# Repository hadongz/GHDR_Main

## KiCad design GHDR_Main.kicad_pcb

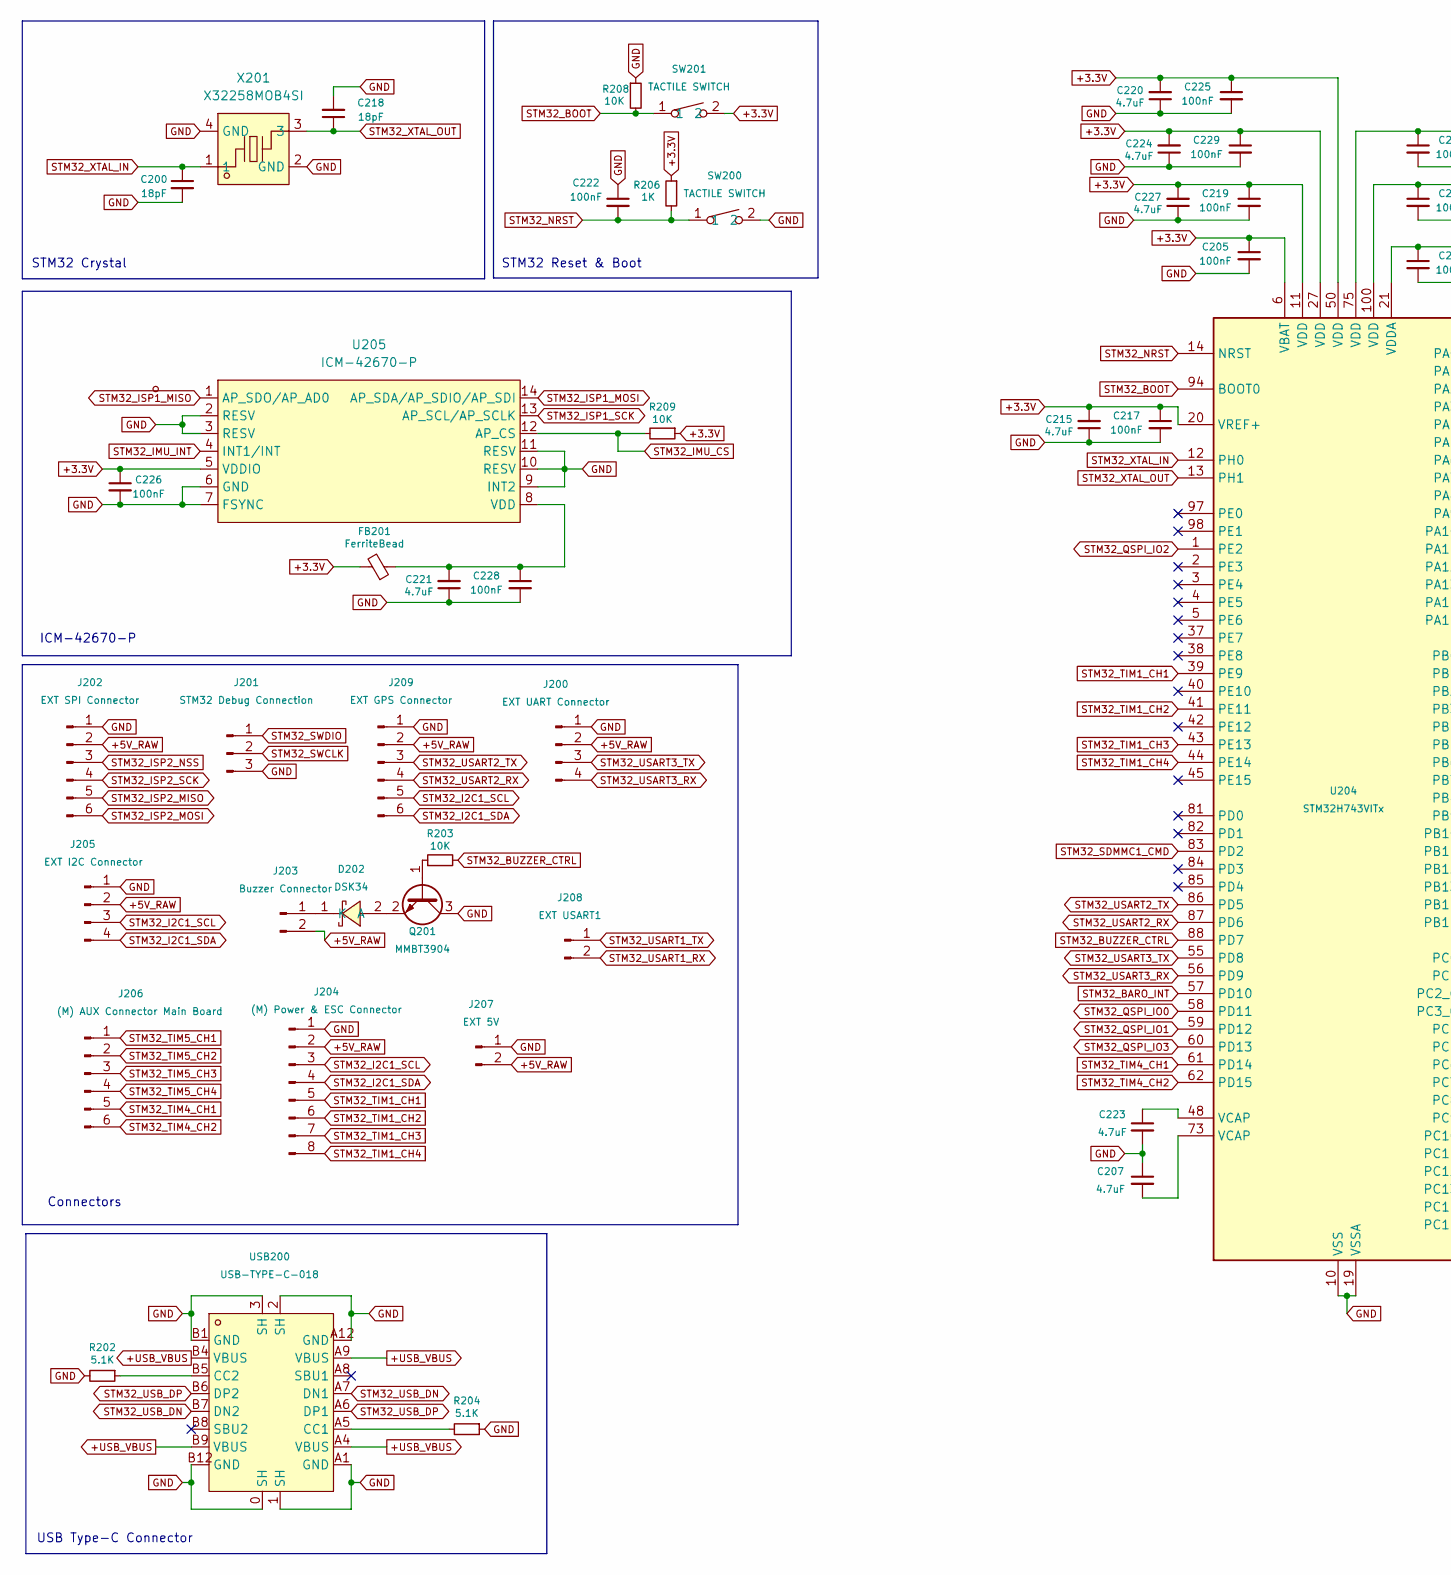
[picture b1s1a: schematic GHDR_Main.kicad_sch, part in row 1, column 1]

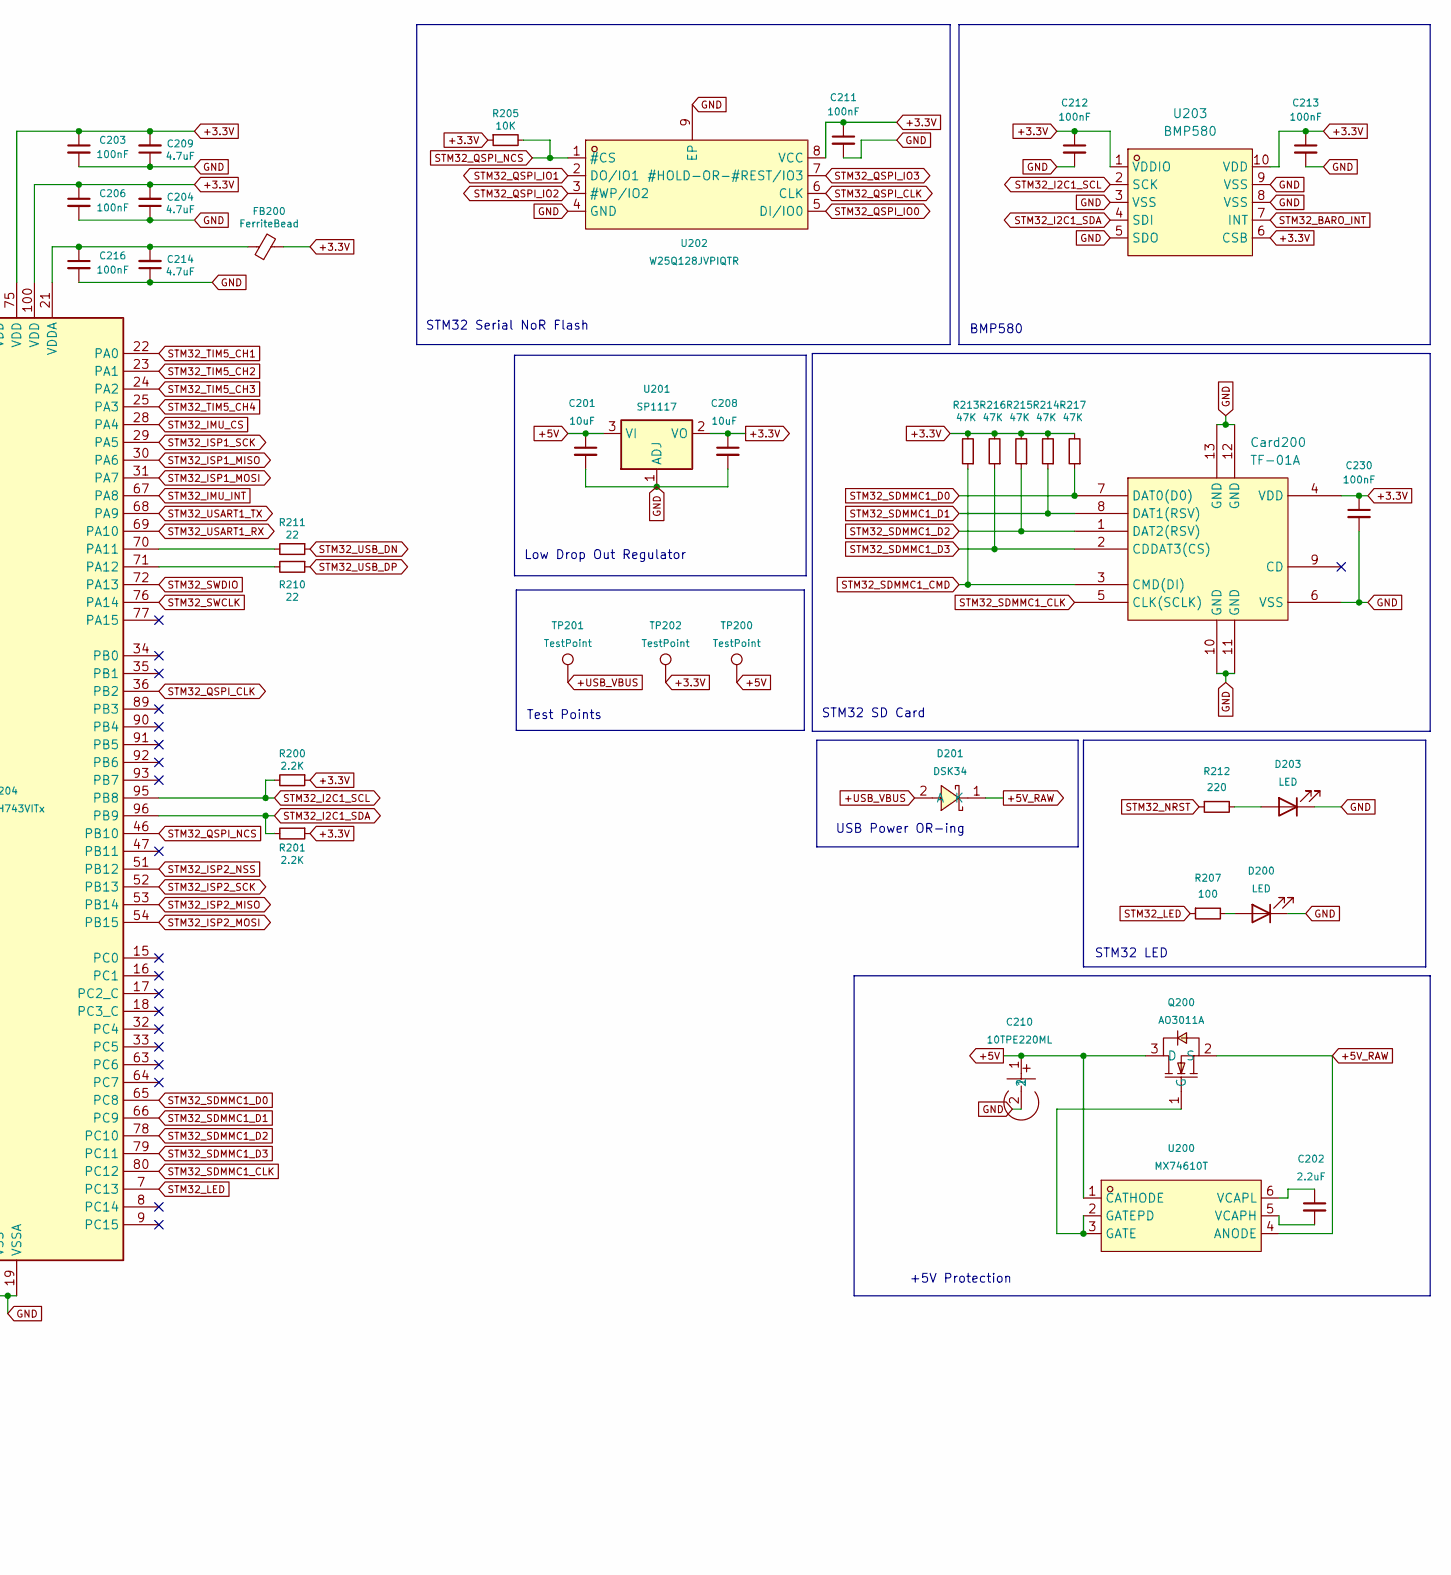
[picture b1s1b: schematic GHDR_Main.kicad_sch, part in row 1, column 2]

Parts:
C200, C218: 18pF; C_0603_1608Metric; LCSC Part C105620
C201, C208: 10uF; C_0805_2012Metric; LCSC Part C7432781
C202: 2.2uF; C_0805_2012Metric; LCSC Part C108719
C203, C205, C206, C211, C212, C213, C216, C217, C219, C222, C225, C226, C228, C229, C230: 100nF; C_0603_1608Metric; LCSC Part C282519
C204, C207, C209, C214, C215, C220, C221, C223, C224, C227: 4.7uF; C_0603_1608Metric; LCSC Part C6119856
C210: 10TPE220ML; CAP-SMD_L7.3-W4.3; LCSC Part C147767
Card200: TF-01A; TF-SMD_TF-01A; LCSC Part C91145
D200: LED; LED_0603_1608Metric; LCSC Part C7371905
D201, D202: DSK34; SOD-123FL_L2.7-W1.8-LS3.8-RD; LCSC Part C727076
D203: LED; LED_0603_1608Metric; LCSC Part C84263
FB200, FB201: FerriteBead; L_0603_1608Metric; LCSC Part C82155
J200: EXT UART Connector; PinHeader_1x04_P2.54mm_Vertical; LCSC Part C3029379
J201: STM32 Debug Connection; PinHeader_1x03_P2.54mm_Vertical_Custom
J202: EXT SPI Connector; PinHeader_1x06_P2.54mm_Vertical; LCSC Part C2886769
J203: Buzzer Connector; PinHeader_1x02_P2.54mm_Vertical; LCSC Part C3029377
J204: (M) Power & ESC Connector; PinHeader_1x08_P2.54mm_Vertical
J205: EXT I2C Connector; PinHeader_1x04_P2.54mm_Vertical; LCSC Part C3029370
J206: (M) AUX Connector Main Board; PinHeader_1x06_P2.54mm_Vertical; LCSC Part C2886769
J207: EXT 5V; PinHeader_1x02_P2.54mm_Vertical; LCSC Part C3029377
J208: EXT USART1; PinHeader_1x02_P2.54mm_Vertical; LCSC Part C3029377
J209: EXT GPS Connector; PinHeader_1x06_P2.54mm_Vertical; LCSC Part C2886769
Q200: AO3011A; SOT-23-3_L2.9-W1.6-P1.90-LS2.8-BR; LCSC Part C49046454
Q201: MMBT3904; SOT-23; LCSC Part C41371422
R200, R201: 2.2K; R_0603_1608Metric; LCSC Part C325591
R202, R204: 5.1K; R_0603_1608Metric; LCSC Part C269716
R203, R205, R208, R209: 10K; R_0603_1608Metric; LCSC Part C25804
R206: 1K; R_0603_1608Metric; LCSC Part C25804
R207: 100; R_0603_1608Metric; LCSC Part C105588
R210, R211: 22; R_0603_1608Metric; LCSC Part C23345
R212: 220; R_0603_1608Metric; LCSC Part C22962
R213, R214, R215, R216, R217: 47K; R_0603_1608Metric; LCSC Part C105579
SW200, SW201: TACTILE SWITCH; KEY-SMD_L4.0-W3.0-LS4.9-1; LCSC Part C49234124
TP200, TP202: TestPoint; TestPoint_Pad_D1.5mm
TP201: TestPoint; TestPoint_Pad_D1.0mm
U200: MX74610T; SOT-23-6_L2.9-W1.6-P0.95-LS2.8-BL-1; LCSC Part C19078229
U201: SP1117; SOT-223-3_TabPin2; LCSC Part C41355114
U202: W25Q128JVPIQTR; WSON-8_L6.0-W5.0-P1.27-BL-EP; LCSC Part C190862
U203: BMP580; LGA-10_L2.0-W2.0-P0.50-TL_BMP580; LCSC Part C22391138
U204: STM32H743VITx; LQFP-100_14x14mm_P0.5mm; LCSC Part C114409
U205: ICM-42670-P; LGA-14_L3.0-W2.5-P0.50-TL_QMI8658A; LCSC Part C3288646
USB200: USB-TYPE-C-018; USB-C_SMD-TYPE-C-31-M-12; LCSC Part C2927038
X201: X32258MOB4SI; CRYSTAL-SMD_4P-L3.2-W2.5-BL; LCSC Part C2682775

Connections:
+3.3V: C203.1, C204.2, C205.1, C206.1, C208.1, C209.2, C211.1, C212.1, C213.1, C215.2, C217.1, C219.1, C220.2, C224.2, C225.1, C226.1, C227.2, C229.1, C230.1, Card200.4 (VDD), FB200.2, FB201.2, R200.1, R201.1, R205.1, R206.1, R209.1, R213.2, R214.2, R215.2, R216.2, R217.2, SW201.2, TP202.1, U201.2 (VO), U202.8 (VCC), U203.1 (VDDIO), U203.6 (CSB), U203.10 (VDD), U204.6 (VBAT), U204.11 (VDD), U204.20 (VREF+), U204.27 (VDD), U204.50 (VDD), U204.75 (VDD), U204.100 (VDD), U205.5 (VDDIO)
+5V: C201.1, C210.1, Q200.3 (D), TP200.1, U200.1 (CATHODE), U201.3 (VI)
+5V_RAW: D201.1 (K), J200.2, J202.2, J203.2, J204.2, J205.2, J207.2, J209.2, Q200.2 (S), U200.4 (ANODE)
+USB_VBUS: D201.2 (A), TP201.1, USB200.A4 (VBUS), USB200.A9 (VBUS), USB200.B4 (VBUS), USB200.B9 (VBUS)
GND: C200.2, C201.2, C203.2, C204.1, C205.2, C206.2, C207.1, C208.2, C209.1, C210.2, C211.2, C212.2, C213.2, C214.1, C215.1, C216.2, C217.2, C218.2, C219.2, C220.1, C221.1, C222.1, C223.2, C224.1, C225.2, C226.2, C227.1, C228.2, C229.2, C230.2, Card200.6 (VSS), Card200.10 (GND), Card200.11 (GND), Card200.12 (GND), Card200.13 (GND), D200.1 (K), D203.1 (K), J200.1, J201.3, J202.1, J204.1, J205.1, J207.1, J209.1, Q201.3 (C), R202.2, R204.1, R208.1, SW200.2, U201.1 (ADJ), U202.4 (GND), U202.9 (EP), U203.3 (VSS), U203.5 (SDO), U203.8 (VSS), U203.9 (VSS), U204.10 (VSS), U204.19 (VSSA), U204.26 (VSS), U204.49 (VSS), U204.74 (VSS), U204.99 (VSS), U205.2 (RESV), U205.3 (RESV), U205.6 (GND), U205.7 (FSYNC), U205.9 (INT2), U205.10 (RESV), U205.11 (RESV), USB200.0 (SH), USB200.1 (SH), USB200.2 (SH), USB200.3 (SH), USB200.A1 (GND), USB200.A12 (GND), USB200.B1 (GND), USB200.B12 (GND), X201.2 (GND), X201.4 (GND)
unnamed: C207.2, U204.73 (VCAP)
unnamed: C223.1, U204.48 (VCAP)
unnamed: D200.2 (A), R207.2
unnamed: D202.2 (A), Q201.2 (E)
unnamed: D202.1 (K), J203.1
unnamed: D203.2 (A), R212.2
unnamed: Q200.1 (G), U200.2 (GATEPD), U200.3 (GATE)
unnamed: Q201.1 (B), R203.1
unnamed: C202.2, U200.5 (VCAPH)
unnamed: C202.1, U200.6 (VCAPL)
unnamed: R211.2, U204.70 (PA11)
unnamed: R210.2, U204.71 (PA12)
unnamed: C214.2, C216.1, FB200.1, U204.21 (VDDA)
unnamed: C221.2, C228.1, FB201.1, U205.8 (VDD)
unnamed: R204.2, USB200.A5 (CC1)
unnamed: R202.1, USB200.B5 (CC2)
STM32_BARO_INT: U203.7 (INT), U204.57 (PD10)
STM32_BOOT: R208.2, SW201.1, U204.94 (BOOT0)
STM32_BUZZER_CTRL: R203.2, U204.88 (PD7)
STM32_I2C1_SCL: J204.3, J205.3, J209.5, R200.2, U203.2 (SCK), U204.95 (PB8)
STM32_I2C1_SDA: J204.4, J205.4, J209.6, R201.2, U203.4 (SDI), U204.96 (PB9)
STM32_IMU_CS: R209.2, U204.28 (PA4), U205.12 (AP_CS)
STM32_IMU_INT: U204.67 (PA8), U205.4 (INT1/INT)
STM32_ISP1_MISO: U204.30 (PA6), U205.1 (AP_SDO/AP_AD0)
STM32_ISP1_MOSI: U204.31 (PA7), U205.14 (AP_SDA/AP_SDIO/AP_SDI)
STM32_ISP1_SCK: U204.29 (PA5), U205.13 (AP_SCL/AP_SCLK)
STM32_ISP2_MISO: J202.5, U204.53 (PB14)
STM32_ISP2_MOSI: J202.6, U204.54 (PB15)
STM32_ISP2_NSS: J202.3, U204.51 (PB12)
STM32_ISP2_SCK: J202.4, U204.52 (PB13)
STM32_LED: R207.1, U204.7 (PC13)
STM32_NRST: C222.2, R206.2, R212.1, SW200.1, U204.14 (NRST)
STM32_QSPI_CLK: U202.6 (CLK), U204.36 (PB2)
STM32_QSPI_IO0: U202.5 (DI/IO0), U204.58 (PD11)
STM32_QSPI_IO1: U202.2 (DO/IO1), U204.59 (PD12)
STM32_QSPI_IO2: U202.3 (#WP/IO2), U204.1 (PE2)
STM32_QSPI_IO3: U202.7 (#HOLD-OR-#REST/IO3), U204.60 (PD13)
STM32_QSPI_NCS: R205.2, U202.1 (#CS), U204.46 (PB10)
STM32_SDMMC1_CLK: Card200.5 (CLK(SCLK)), U204.80 (PC12)
STM32_SDMMC1_CMD: Card200.3 (CMD(DI)), R213.1, U204.83 (PD2)
STM32_SDMMC1_D0: Card200.7 (DAT0(D0)), R217.1, U204.65 (PC8)
STM32_SDMMC1_D1: Card200.8 (DAT1(RSV)), R214.1, U204.66 (PC9)
STM32_SDMMC1_D2: Card200.1 (DAT2(RSV)), R215.1, U204.78 (PC10)
STM32_SDMMC1_D3: Card200.2 (CDDAT3(CS)), R216.1, U204.79 (PC11)
STM32_SWCLK: J201.2, U204.76 (PA14)
STM32_SWDIO: J201.1, U204.72 (PA13)
STM32_TIM1_CH1: J204.5, U204.39 (PE9)
STM32_TIM1_CH2: J204.6, U204.41 (PE11)
STM32_TIM1_CH3: J204.7, U204.43 (PE13)
STM32_TIM1_CH4: J204.8, U204.44 (PE14)
STM32_TIM4_CH1: J206.5, U204.61 (PD14)
STM32_TIM4_CH2: J206.6, U204.62 (PD15)
STM32_TIM5_CH1: J206.1, U204.22 (PA0)
STM32_TIM5_CH2: J206.2, U204.23 (PA1)
STM32_TIM5_CH3: J206.3, U204.24 (PA2)
STM32_TIM5_CH4: J206.4, U204.25 (PA3)
STM32_USART1_RX: J208.2, U204.69 (PA10)
STM32_USART1_TX: J208.1, U204.68 (PA9)
STM32_USART2_RX: J209.4, U204.87 (PD6)
STM32_USART2_TX: J209.3, U204.86 (PD5)
STM32_USART3_RX: J200.4, U204.56 (PD9)
STM32_USART3_TX: J200.3, U204.55 (PD8)
STM32_USB_DN: R211.1, USB200.A7 (DN1), USB200.B7 (DN2)
STM32_USB_DP: R210.1, USB200.A6 (DP1), USB200.B6 (DP2)
STM32_XTAL_IN: C200.1, U204.12 (PH0), X201.1
STM32_XTAL_OUT: C218.1, U204.13 (PH1), X201.3

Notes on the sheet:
Low Drop Out Regulator
STM32 SD Card
BMP580
+5V Protection
STM32 Serial NoR Flash
Connectors
STM32 Crystal
STM32 LED
STM32 Reset & Boot
USB Type-C Connector
ICM-42670-P
Test Points
USB Power OR-ing

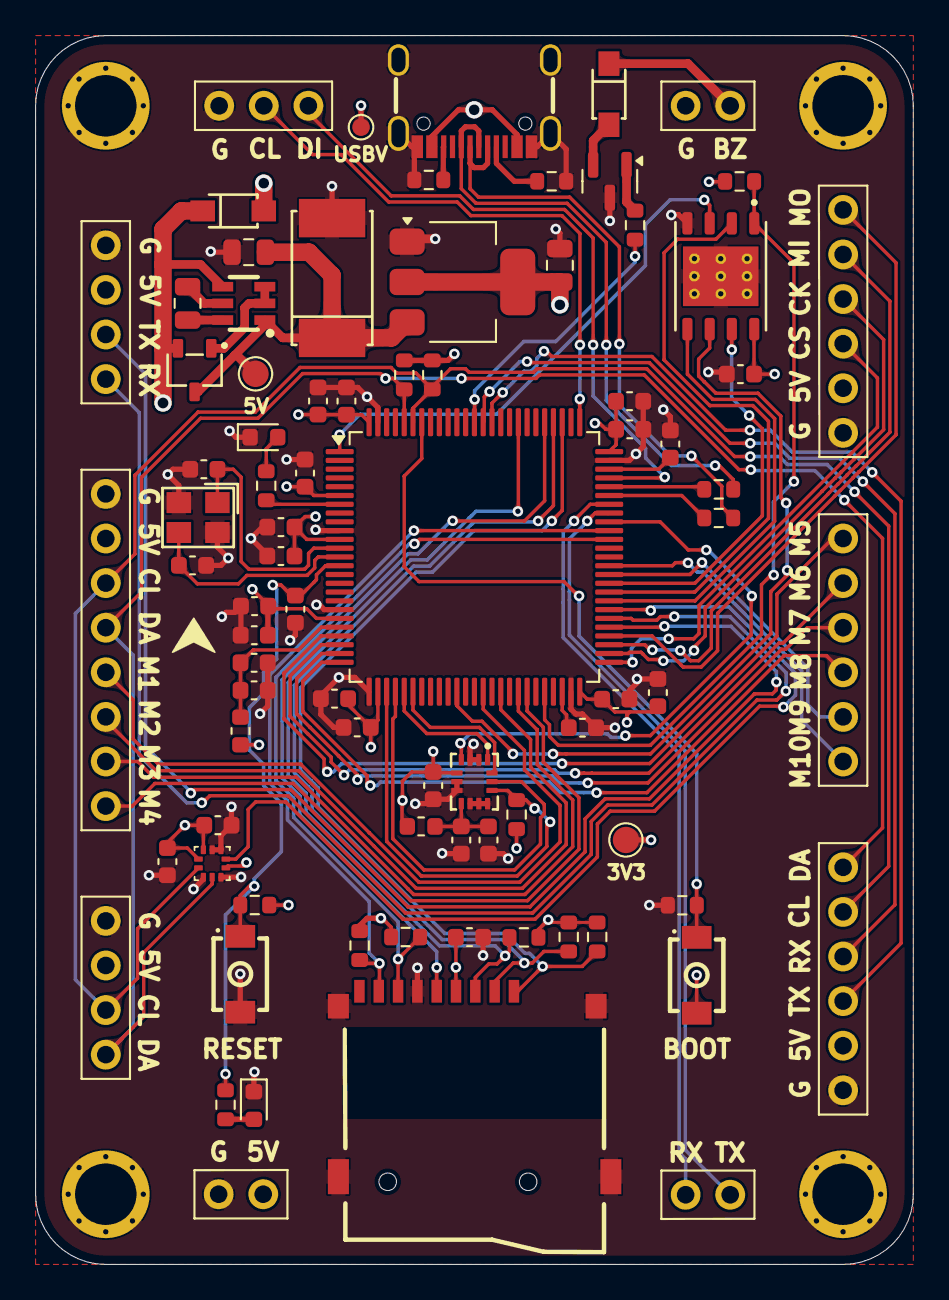
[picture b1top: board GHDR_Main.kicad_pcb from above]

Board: 4 copper layers, 50.0 x 70.0 mm, 81 parts (0 on the bottom side), 71 nets.

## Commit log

2025-10-19 [MAIN BOARD] Initial Commit
2025-10-20 feat: update
2025-10-26 feat: update for github
2025-11-08 feat: update for fab
2025-12-07 feat: change crystal
